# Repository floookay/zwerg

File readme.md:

# zwerg

The zwerg is a 3x6 (well technically 4x6 I guess?) split ortholinear 40% keyboard.
It's heavily inspired by [RGBKB.net's Sol 3](https://rgbkb.net/collections/sol-3) of which I own two and absolutely adore.

> [!Warning]  
> Please note that this design only works with a slim usb-c cable/connector (5.5mm).

KLE: <https://www.keyboard-layout-editor.com/#/gists/f58560b496cb75689321efaddc96187e>

The typing and tenting angle can be freely adjusted in the OpenSCAD file. I printed mine with a typing angle of 2° and tenting of 5°.

## what you need

- [ ] 2x zwerg pcbs (upload [zwerg.zip](./pcb/production/zwerg.zip) to a pcb manufacturer)
- [ ] 2x [0xCB geminis](https://keeb.supply/products/0xcb-gemini)
- [ ] 50x switches
- [ ] 50x diodes (1N4148W smd or tht)
- [ ] 2x trrs jacks
- [ ] 2x [M2x3x3 heat inserts](https://sea3d.de/10-Stueck-Gewindeeinsatz-M2-Raendelmutter-Einpressmutter-Heat-Set-Insert)
- [ ] 2x M2 5-8mm screws
- [ ] 10x 7x1.9mm o-rings
- [ ] 8x 7x1mm bumpons
- [ ] 2x 3d-printed zwerg case halves (print with supports if needed)
- [ ] *optional* 2x 3d-printed zwerg plates

Building this keyboard is pretty straight forward I think. The only thing you need to look out for is that you solder all components on the same side (same goes for the mirrored pcb). Don't over tighten the screw that attaches the pcb to the case, it's supposed be screwed in lightly.

This keyboard is powered by qmk firmware, see [here](https://github.com/qmk/qmk_firmware/tree/master/keyboards/zwerg). Use the reset buttons on the Gemini for flashing the keyboard.

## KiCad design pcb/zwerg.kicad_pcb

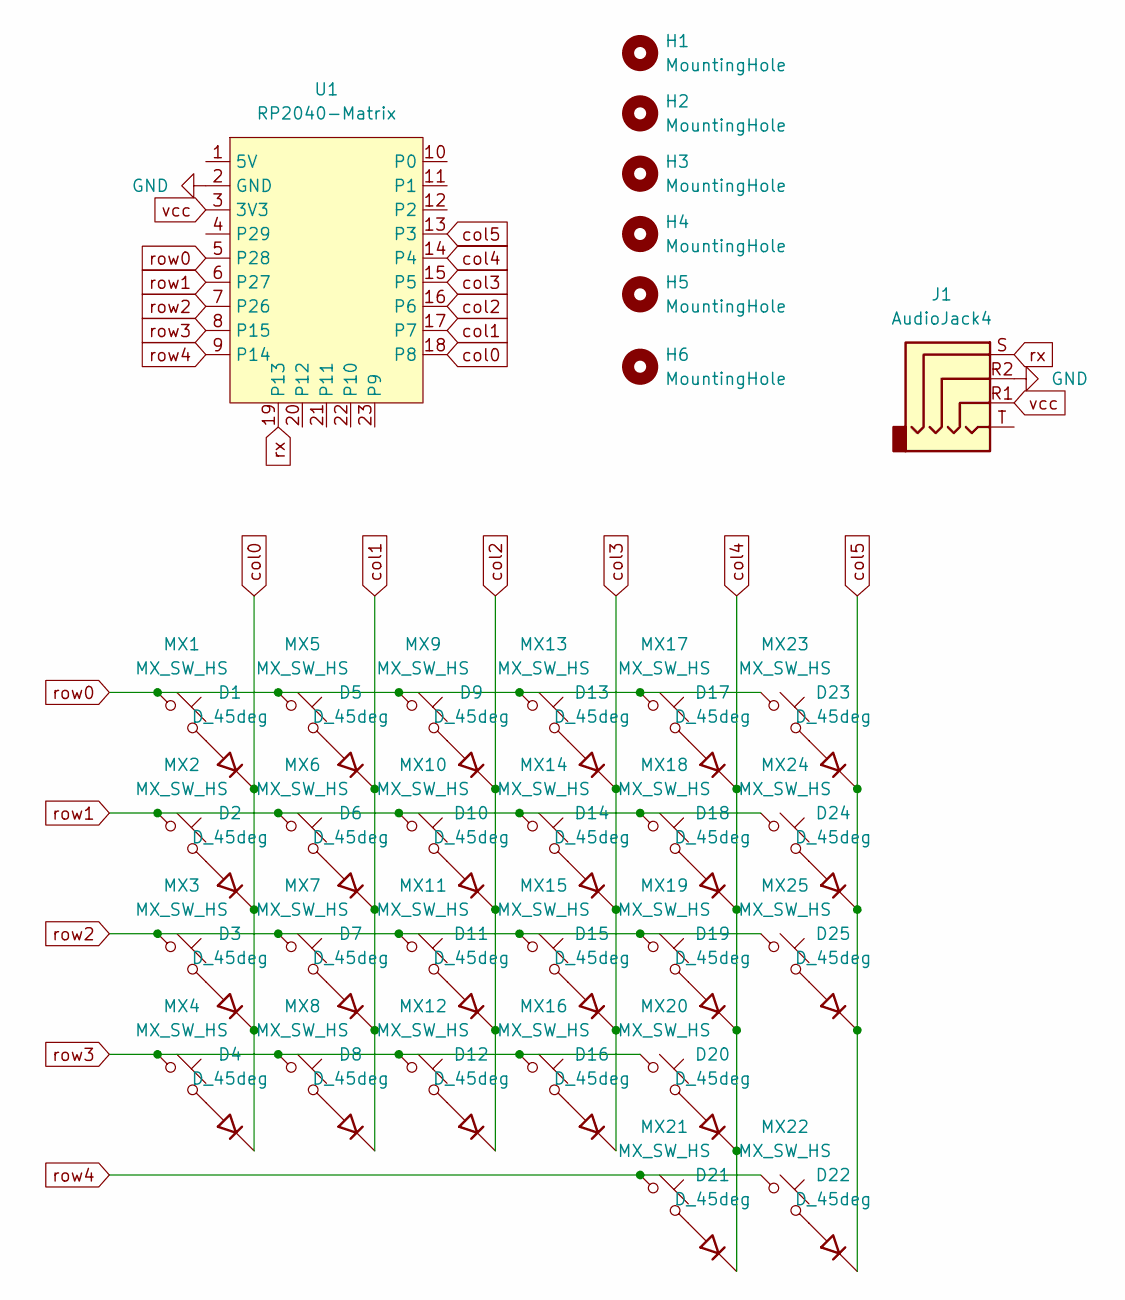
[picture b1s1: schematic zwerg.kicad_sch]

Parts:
D1, D2, D3, D4, D5, D6, D7, D8, D9, D10, D11, D12, D13, D14, D15, D16, D17, D18, D19, D20, D21, D22, D23, D24, D25: D_45deg; D3_TH_SMD
H1, H2, H3, H4, H5: MountingHole; MountingHole_4.3mm_M4
H6: MountingHole; MountingHole_2.2mm_M2_DIN965_Pad_TopBottom
J1: AudioJack4; CON_MJ-4PP-9_Reversible
MX1, MX2, MX3, MX4, MX5, MX6, MX7, MX8, MX9, MX10, MX11, MX12, MX13, MX14, MX15, MX16, MX17, MX18, MX19, MX20, MX21, MX22, MX23, MX24, MX25: MX_SW_HS; SW_MX_Reversible_1u
U1: RP2040-Matrix; RP2040-Matrix_fb

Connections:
GND: J1.R2, U1.2 (GND)
unnamed: D1.2 (A), MX1.2
unnamed: D2.2 (A), MX2.2
unnamed: D3.2 (A), MX3.2
unnamed: D4.2 (A), MX4.2
unnamed: D5.2 (A), MX5.2
unnamed: D6.2 (A), MX6.2
unnamed: D7.2 (A), MX7.2
unnamed: D8.2 (A), MX8.2
unnamed: D9.2 (A), MX9.2
unnamed: D10.2 (A), MX10.2
unnamed: D11.2 (A), MX11.2
unnamed: D12.2 (A), MX12.2
unnamed: D13.2 (A), MX13.2
unnamed: D14.2 (A), MX14.2
unnamed: D15.2 (A), MX15.2
unnamed: D16.2 (A), MX16.2
unnamed: D17.2 (A), MX17.2
unnamed: D18.2 (A), MX18.2
unnamed: D19.2 (A), MX19.2
unnamed: D20.2 (A), MX20.2
unnamed: D21.2 (A), MX21.2
unnamed: D22.2 (A), MX22.2
unnamed: D23.2 (A), MX23.2
unnamed: D24.2 (A), MX24.2
unnamed: D25.2 (A), MX25.2
col0: D1.1 (K), D2.1 (K), D3.1 (K), D4.1 (K), U1.18 (P8)
col1: D5.1 (K), D6.1 (K), D7.1 (K), D8.1 (K), U1.17 (P7)
col2: D9.1 (K), D10.1 (K), D11.1 (K), D12.1 (K), U1.16 (P6)
col3: D13.1 (K), D14.1 (K), D15.1 (K), D16.1 (K), U1.15 (P5)
col4: D17.1 (K), D18.1 (K), D19.1 (K), D20.1 (K), D21.1 (K), U1.14 (P4)
col5: D22.1 (K), D23.1 (K), D24.1 (K), D25.1 (K), U1.13 (P3)
row0: MX1.1, MX5.1, MX9.1, MX13.1, MX17.1, MX23.1, U1.5 (P28)
row1: MX2.1, MX6.1, MX10.1, MX14.1, MX18.1, MX24.1, U1.6 (P27)
row2: MX3.1, MX7.1, MX11.1, MX15.1, MX19.1, MX25.1, U1.7 (P26)
row3: MX4.1, MX8.1, MX12.1, MX16.1, MX20.1, U1.8 (P15)
row4: MX21.1, MX22.1, U1.9 (P14)
rx: J1.S, U1.19 (P13)
vcc: J1.R1, U1.3 (3V3)

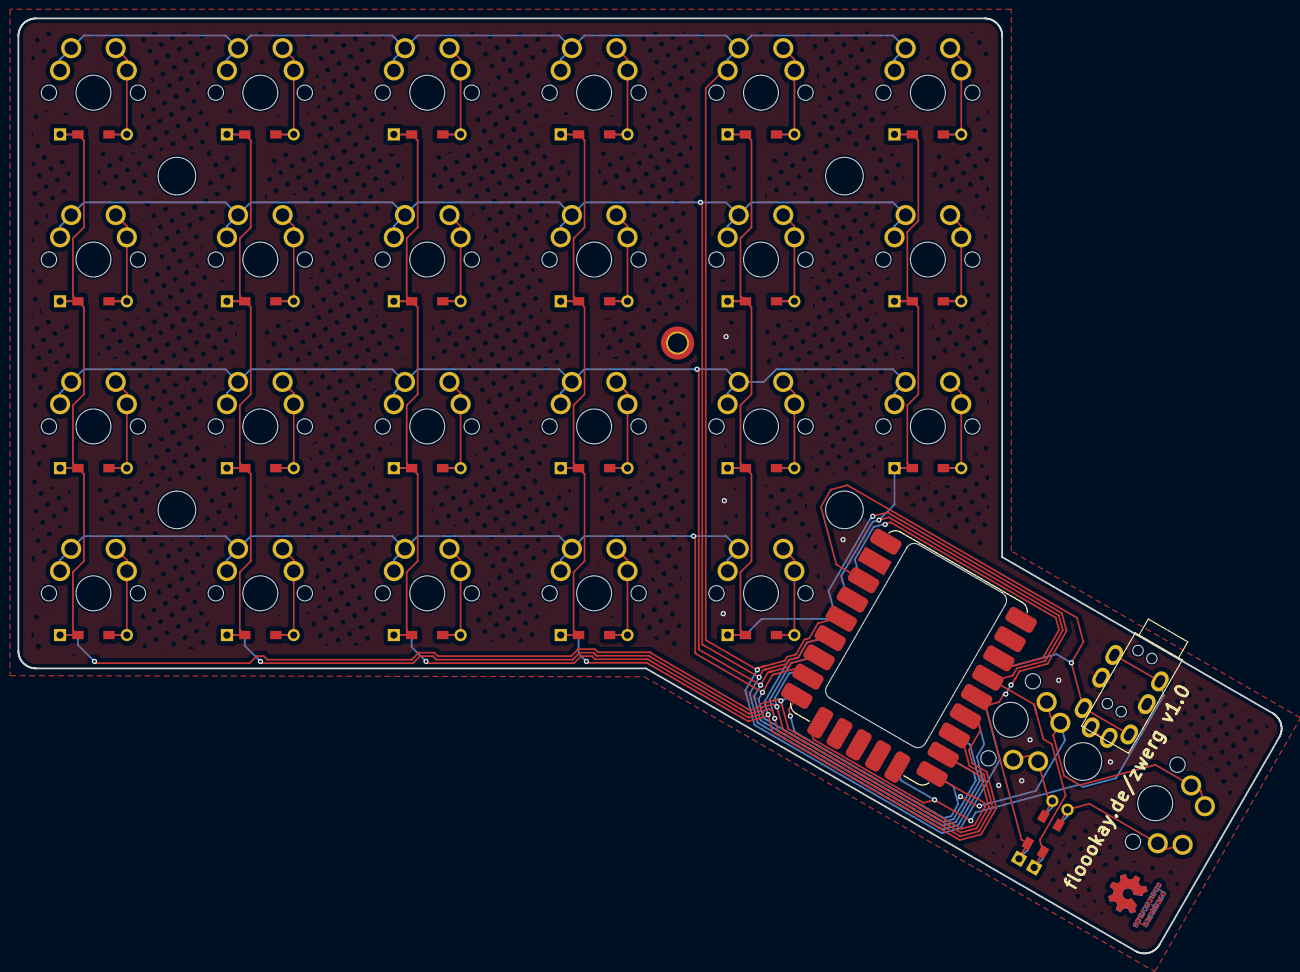
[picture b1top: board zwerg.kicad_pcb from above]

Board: 2 copper layers, 144.2 x 106.7 mm, 58 parts (0 on the bottom side), 39 nets.

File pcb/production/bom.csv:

Designator,Footprint,Quantity,Value,LCSC Part #
"D1, D10, D11, D12, D13, D14, D15, D16, D17, D18, D19, D2, D20, D21, D22, D23, D24, D25, D3, D4, D5, D6, D7, D8, D9",D3_TH_SMD,25,D_45deg,
J1,CON_MJ-4PP-9_Reversible,1,AudioJack4,
"MX1, MX10, MX11, MX12, MX13, MX14, MX15, MX16, MX17, MX18, MX19, MX2, MX20, MX21, MX22, MX23, MX24, MX25, MX3, MX4, MX5, MX6, MX7, MX8, MX9",SW_MX_Reversible_1u,25,MX_SW_HS,

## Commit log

2024-11-30 added case files
2024-11-30 added readme
2024-12-04 added pcb draft
2024-12-06 updated pcb and case v1.0
2024-12-20 increased clearance and added screw hole to plate
2025-01-07 added feet and opening for trrs connector
2025-01-07 shrinked usbc hole stlightly
2025-02-01 added code workspace
2025-02-01 added link to qmk firmware
2025-02-01 fixed typo
2025-02-14 fixed link
2025-02-15 oops, forgot the license
2025-03-07 Update qmk repo link
2025-03-07 added notes about typing and tenting angle
